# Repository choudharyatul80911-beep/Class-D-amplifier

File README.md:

# CLASS-D-AMPLIFIER
Circuit and PCB Design on Kicad Software
# 555 Timer Class D Audio Amplifier

This repository contains the KiCad design files (Schematic and PCB layout) for a simple yet effective **Class D Audio Amplifier** based on the widespread **NE555 Timer IC**.

Unlike Class AB amplifiers which dissipate a lot of heat, this Class D design utilizes Pulse Width Modulation (PWM) to achieve higher efficiency, driving a push-pull output stage with TIP41 and TIP42 transistors.

## 📸 Project Visuals

### 3D Visualization

*A 3D rendering of the final PCB assembly showing component placement.*

### Schematic Diagram

*The circuit logic showing the 555 Timer configured as a PWM generator driving the output transistors.*

### PCB Layout

*The compact trace routing and footprint layout designed in KiCad.*

---

## 🚀 Features
* **High Efficiency:** Uses Class D topology (PWM modulation).
* **Simple Components:** Built around the common NE555 Timer and generic power transistors.
* **Compact Design:** Small form factor PCB suitable for portable audio projects.
* **Power Supply:** Designed for a standard 9V battery input.

## 🛠 Component List (BOM)
To build this project, you will need the following key components:

| Component | Value/Type | Description |
| :--- | :--- | :--- |
| **U1** | NE555 | Timer IC (DIP-8 or SMD) |
| **Q1** | TIP41 | NPN Power Transistor |
| **Q2** | TIP42 | PNP Power Transistor |
| **L1** | 30mH | Inductor (Output Filter) |
| **J1, J2, J3** | Screw Terminals | For Power, Output, and Signal |
| **C1, C2, etc.** | Various | Ceramic/Electrolytic Capacitors (see schematic) |
| **R1, R2, etc.** | Various | Resistors (see schematic) |

## ⚙️ How It Works
1.  **Input:** The analog audio signal enters via the `Signal` terminal.
2.  **Modulation:** The **NE555 Timer** is configured in an astable mode but modified so that the audio input modulates the pulse width of the output square wave (PWM).
3.  **Amplification:** The PWM signal drives the **TIP41** and **TIP42** transistors, which act as high-speed switches.
4.  **Filtering:** The output LC filter (Inductor L1 and capacitors) removes the high-frequency switching noise, leaving behind the amplified audio signal to drive the speaker.

## 📂 Repository Structure
* `*.kicad_pro` - Project file.
* `*.kicad_sch` - Schematic file.
* `*.kicad_pcb` - PCB Layout file.
* `/images` - Project screenshots and renders.

## 💻 Software Used
This project was designed using **KiCad**, an open-source electronics design automation suite.

## 📝 Author
**Atul Choudhary** [GitHub Profile](https://github.com/choudharyatul80911-beep)

---
*If you find this project useful, please give it a star! ⭐*

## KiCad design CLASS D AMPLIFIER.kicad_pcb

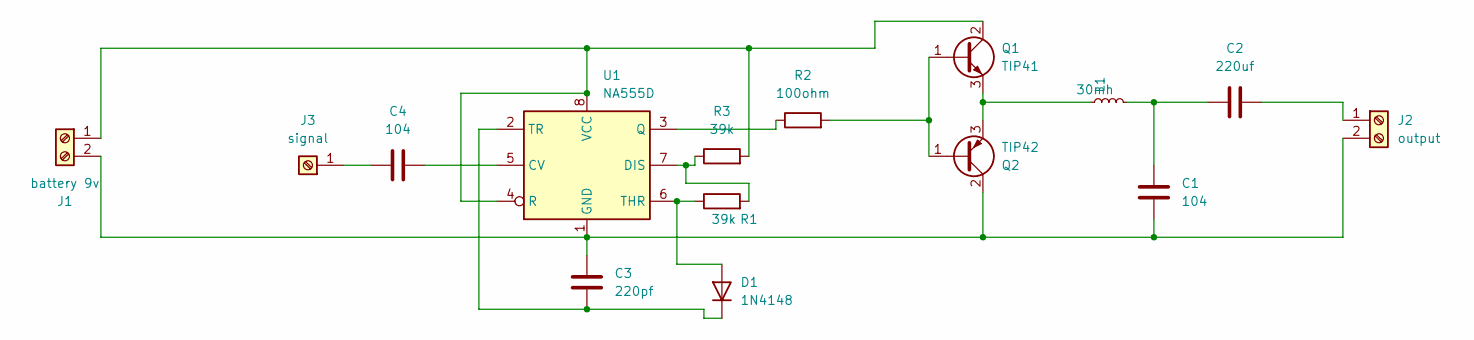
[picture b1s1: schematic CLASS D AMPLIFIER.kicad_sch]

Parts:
C1, C4: 104; C_0201_0603Metric
C2: 220uf; C_0201_0603Metric
C3: 220pf; C_0201_0603Metric
D1: 1N4148; D_DO-35_SOD27_P7.62mm_Horizontal
J1: battery 9v; TerminalBlock_MetzConnect_Type011_RT05502HBLC_1x02_P5.00mm_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
J2: output; TerminalBlock_MetzConnect_Type011_RT05502HBLC_1x02_P5.00mm_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
J3: signal; TerminalBlock_Degson_DG250-3.5-01P_1x01_P3.50mm_45Degree
L1: 30mh; L_6.3x6.3_H3
Q1: TIP41; TO-220-3_Vertical
Q2: TIP42; TO-220-3_Vertical
R1, R3: 39k; R_0201_0603Metric
R2: 100ohm; R_0201_0603Metric
U1: NA555D; SOIC-8_3.9x4.9mm_P1.27mm

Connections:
unnamed: C1.1, C2.1, L1.2
unnamed: D1.2 (A), R1.1, U1.6 (THR)
unnamed: C3.2, D1.1 (K), U1.2 (TR)
unnamed: J1.1, Q1.2 (C), R3.2, U1.4 (R), U1.8 (VCC)
unnamed: C1.2, C3.1, J1.2, J2.2, Q2.2 (C), U1.1 (GND)
unnamed: C2.2, J2.1
unnamed: C4.1, J3.1
unnamed: Q1.1 (B), Q2.1 (B), R2.2
unnamed: L1.1, Q1.3 (E), Q2.3 (E)
unnamed: C4.2, U1.5 (CV)
unnamed: R1.2, R3.1, U1.7 (DIS)
unnamed: R2.1, U1.3 (Q)

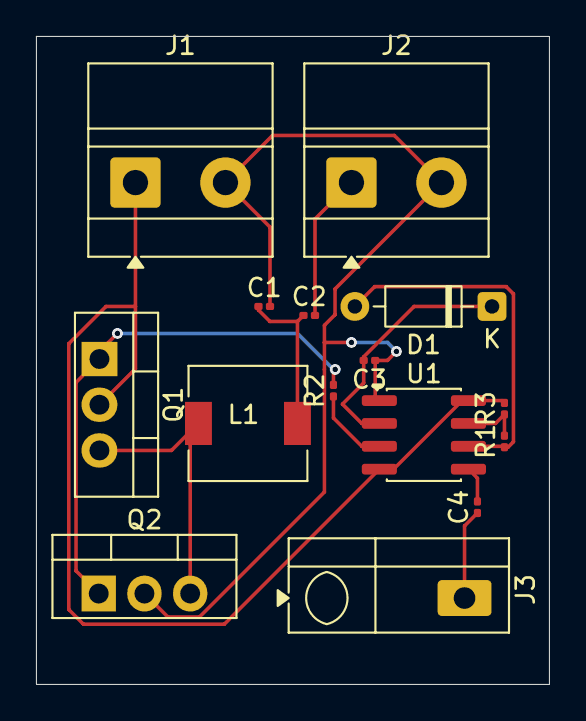
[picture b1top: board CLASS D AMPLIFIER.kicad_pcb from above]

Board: 2 copper layers, 28.5 x 36.0 mm, 15 parts (0 on the bottom side), 12 nets.

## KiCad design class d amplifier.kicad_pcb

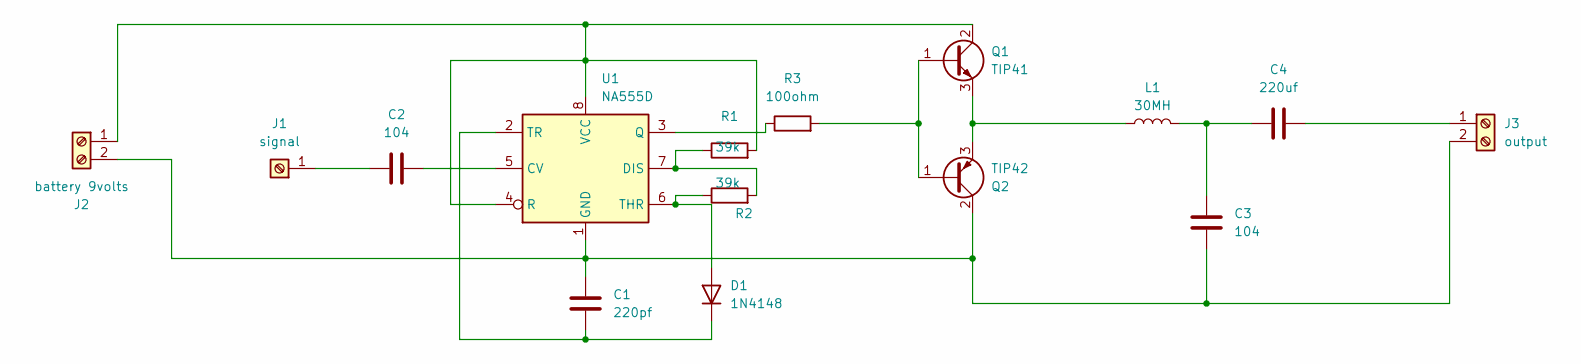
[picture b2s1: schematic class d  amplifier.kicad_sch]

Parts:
C1: 220pf; C_Disc_D12.0mm_W4.4mm_P7.75mm
C2, C3: 104; C_Disc_D12.0mm_W4.4mm_P7.75mm
C4: 220uf; C_Disc_D12.0mm_W4.4mm_P7.75mm
D1: 1N4148; D_DO-35_SOD27_P7.62mm_Horizontal
J1: signal; TerminalBlock_Degson_DG250-3.5-01P_1x01_P3.50mm_45Degree
J2: battery 9volts; TerminalBlock_MaiXu_MX126-5.0-02P_1x02_P5.00mm
J3: output; TerminalBlock_MaiXu_MX126-5.0-02P_1x02_P5.00mm
L1: 30MH; L_Toroid_Horizontal_D16.8mm_P14.70mm_Vishay_TJ3_BigPads
Q1: TIP41; TO-220-3_Vertical
Q2: TIP42; TO-220-3_Vertical
R1, R2: 39k; R_Axial_DIN0617_L17.0mm_D6.0mm_P7.62mm_Vertical
R3: 100ohm; R_Axial_DIN0617_L17.0mm_D6.0mm_P7.62mm_Vertical
U1: NA555D; SOIC-8_3.9x4.9mm_P1.27mm

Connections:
unnamed: C3.1, C4.1, L1.2
unnamed: D1.2 (A), R2.1, U1.6 (THR)
unnamed: C1.1, D1.1 (K), U1.2 (TR)
unnamed: C2.1, J1.1
unnamed: J2.1, Q1.2 (C), R1.2, U1.4 (R), U1.8 (VCC)
unnamed: C1.2, C3.2, J2.2, J3.2, Q2.2 (C), U1.1 (GND)
unnamed: C4.2, J3.1
unnamed: Q1.1 (B), Q2.1 (B), R3.2
unnamed: L1.1, Q1.3 (E), Q2.3 (E)
unnamed: C2.2, U1.5 (CV)
unnamed: R1.1, R2.2, U1.7 (DIS)
unnamed: R3.1, U1.3 (Q)

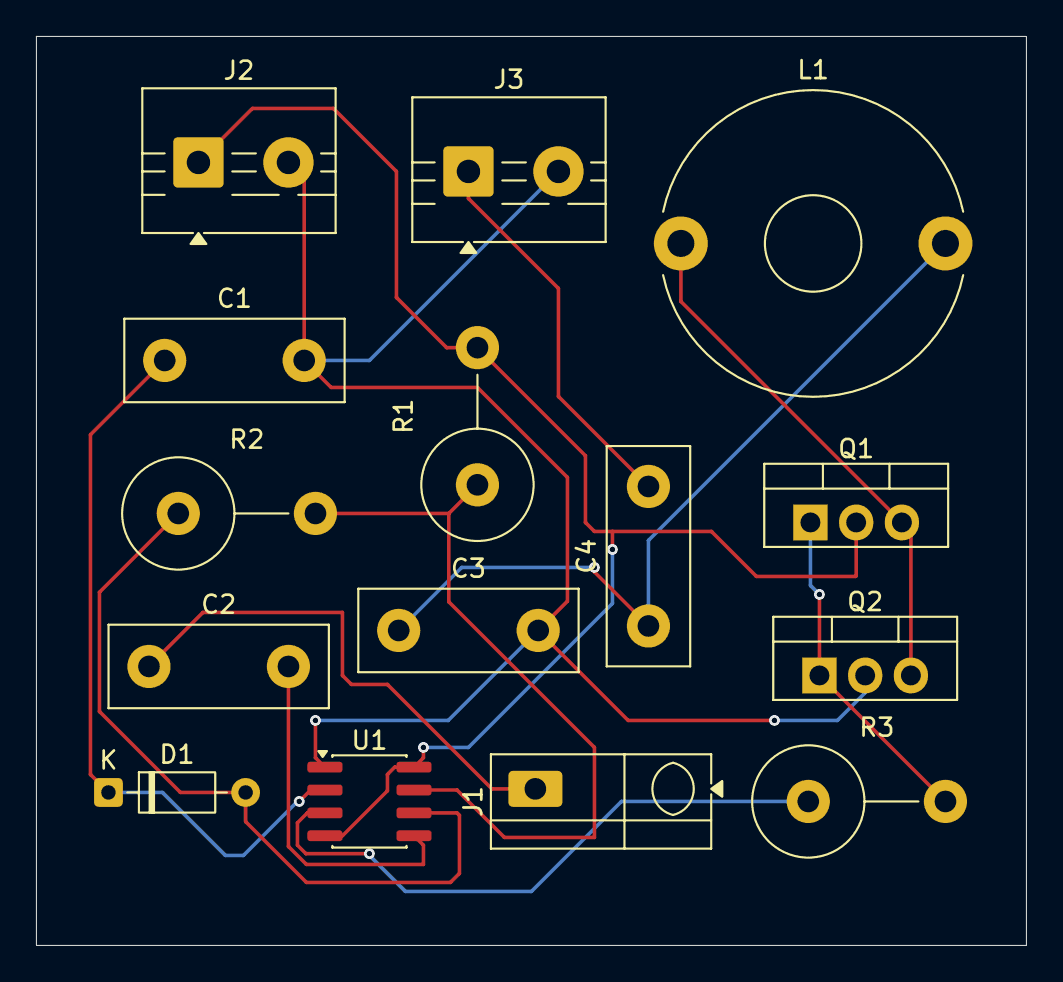
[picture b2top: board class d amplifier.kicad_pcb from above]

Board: 2 copper layers, 55.0 x 50.5 mm, 15 parts (0 on the bottom side), 12 nets.

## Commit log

2025-12-23 Create images
